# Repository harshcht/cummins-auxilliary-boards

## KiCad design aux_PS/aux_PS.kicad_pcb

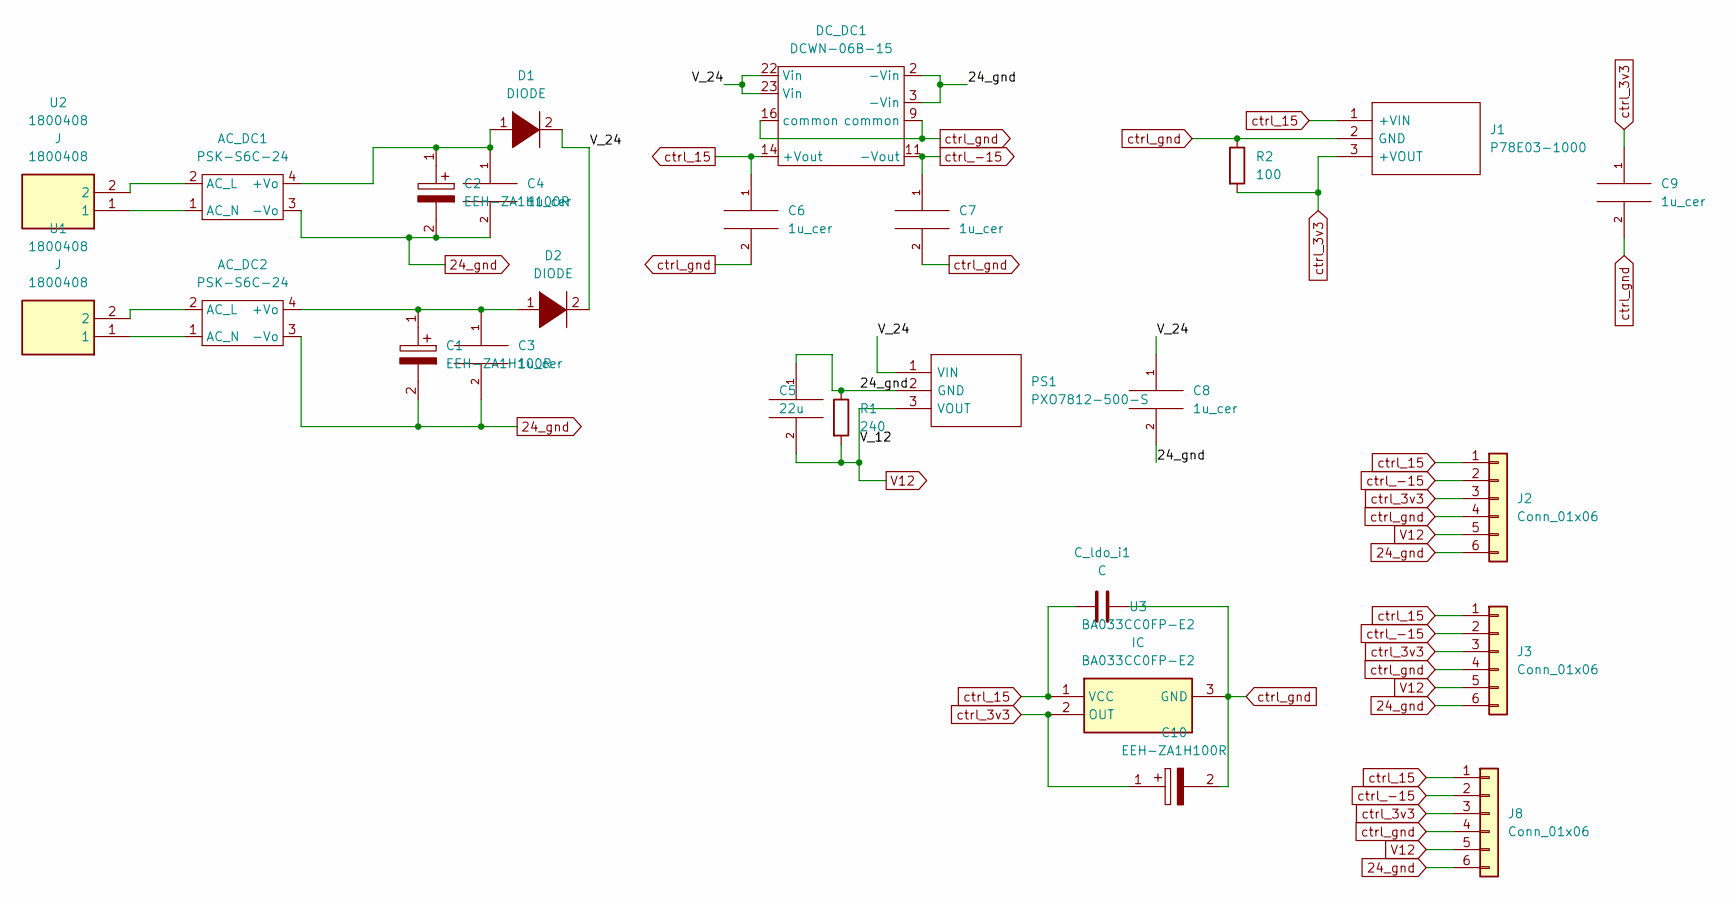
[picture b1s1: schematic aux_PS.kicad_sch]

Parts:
AC_DC1, AC_DC2: PSK-S6C-24; PSKS6C24
C1, C2, C10: EEH-ZA1H100R; EEHZA1H100R; Mouser Part Number 667-EEH-ZA1H100R
C3, C4, C6, C7, C8, C9: 1u_cer; C_1206_3216Metric_Pad1.33x1.80mm_HandSolder
C5: 22u; R_1206_3216Metric_Pad1.30x1.75mm_HandSolder
C_ldo_i1: C; C_1206_3216Metric_Pad1.33x1.80mm_HandSolder
D1, D2: DIODE; D_1206_3216Metric_Pad1.42x1.75mm_HandSolder
DC_DC1: DCWN-06B-15; DCWN06B15
J1: P78E03-1000; P78E031000; Mouser Part Number 490-P78E03-1000
J2, J3, J8: Conn_01x06; PinSocket_1x06_P2.54mm_Vertical
PS1: PXO7812-500-S; PXO7812500S; Mouser Part Number 490-PXO7812-500-S
R1: 240; R_1206_3216Metric_Pad1.30x1.75mm_HandSolder
R2: 100; R_1206_3216Metric_Pad1.30x1.75mm_HandSolder
U1, U2: 1800408; Mouser Part Number 651-1800408
U3: BA033CC0FP-E2; ROHM_TO-252-3; Mouser Part Number 755-BA033CC0FP-E2

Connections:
24_gnd: AC_DC1.3 (-Vo), AC_DC2.3 (-Vo), C1.2, C2.2, C3.2, C4.2, C5.1, C8.2, DC_DC1.2 (-Vin), DC_DC1.3 (-Vin), J2.6, J3.6, J8.6, PS1.2 (GND), R1.1
/V_24: C8.1, D1.2 (A), D2.2 (A), DC_DC1.22 (Vin), DC_DC1.23 (Vin), PS1.1 (VIN)
unnamed: AC_DC1.1 (AC_N), U2.1
unnamed: AC_DC1.2 (AC_L), U2.2
unnamed: AC_DC1.4 (+Vo), C2.1, C4.1, D1.1 (K)
unnamed: AC_DC2.1 (AC_N), U1.1
unnamed: AC_DC2.2 (AC_L), U1.2
unnamed: AC_DC2.4 (+Vo), C1.1, C3.1, D2.1 (K)
V12: C5.2, J2.5, J3.5, J8.5, PS1.3 (VOUT), R1.2
ctrl_3v3: C9.1, C10.1, J1.3 (+VOUT), J2.3, J3.3, J8.3, R2.2, U3.2 (OUT)
ctrl_15: C6.1, C_ldo_i1.2, DC_DC1.14 (+Vout), J1.1 (+VIN), J2.1, J3.1, J8.1, U3.1 (VCC)
ctrl_-15: C7.1, DC_DC1.11 (-Vout), J2.2, J3.2, J8.2
ctrl_gnd: C6.2, C7.2, C9.2, C10.2, C_ldo_i1.1, DC_DC1.9 (common), DC_DC1.16 (common), J1.2 (GND), J2.4, J3.4, J8.4, R2.1, U3.3 (GND)

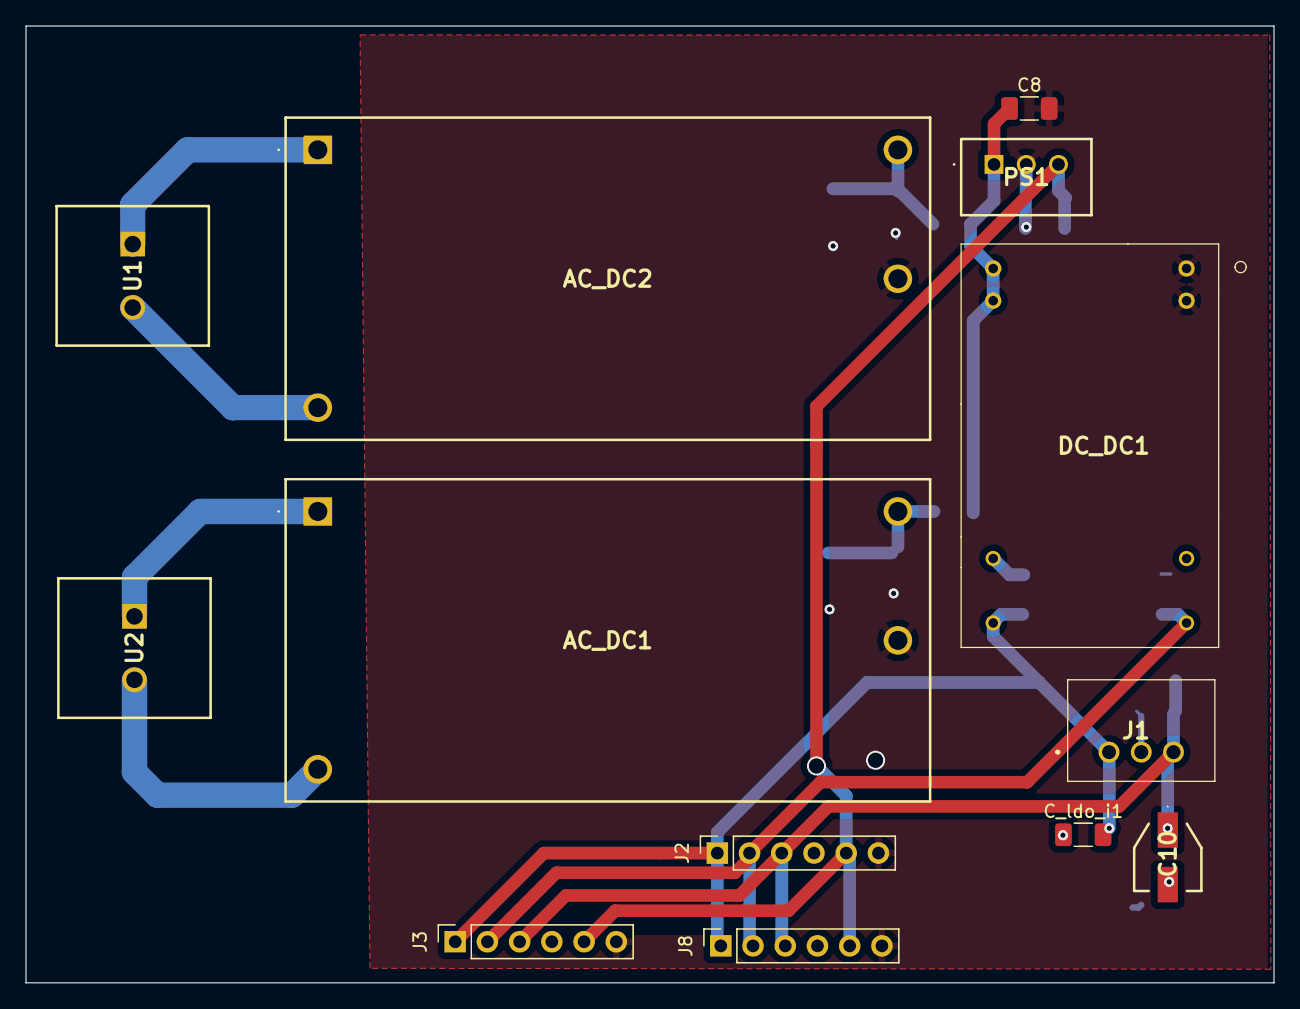
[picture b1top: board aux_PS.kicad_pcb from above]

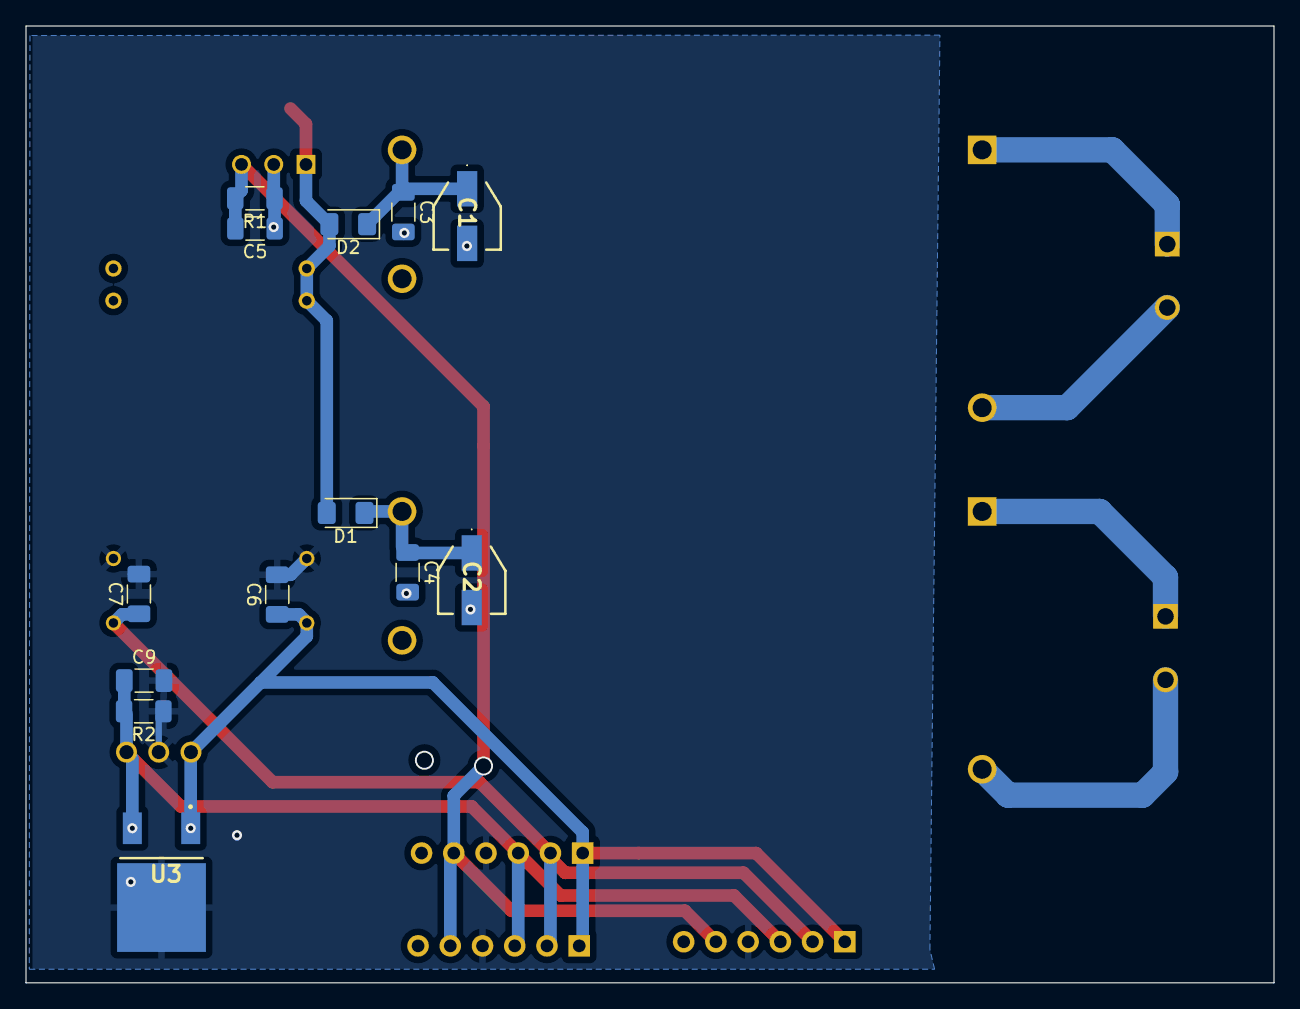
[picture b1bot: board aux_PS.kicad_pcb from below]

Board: 2 copper layers, 98.4 x 75.4 mm, 26 parts (13 on the bottom side), 13 nets.

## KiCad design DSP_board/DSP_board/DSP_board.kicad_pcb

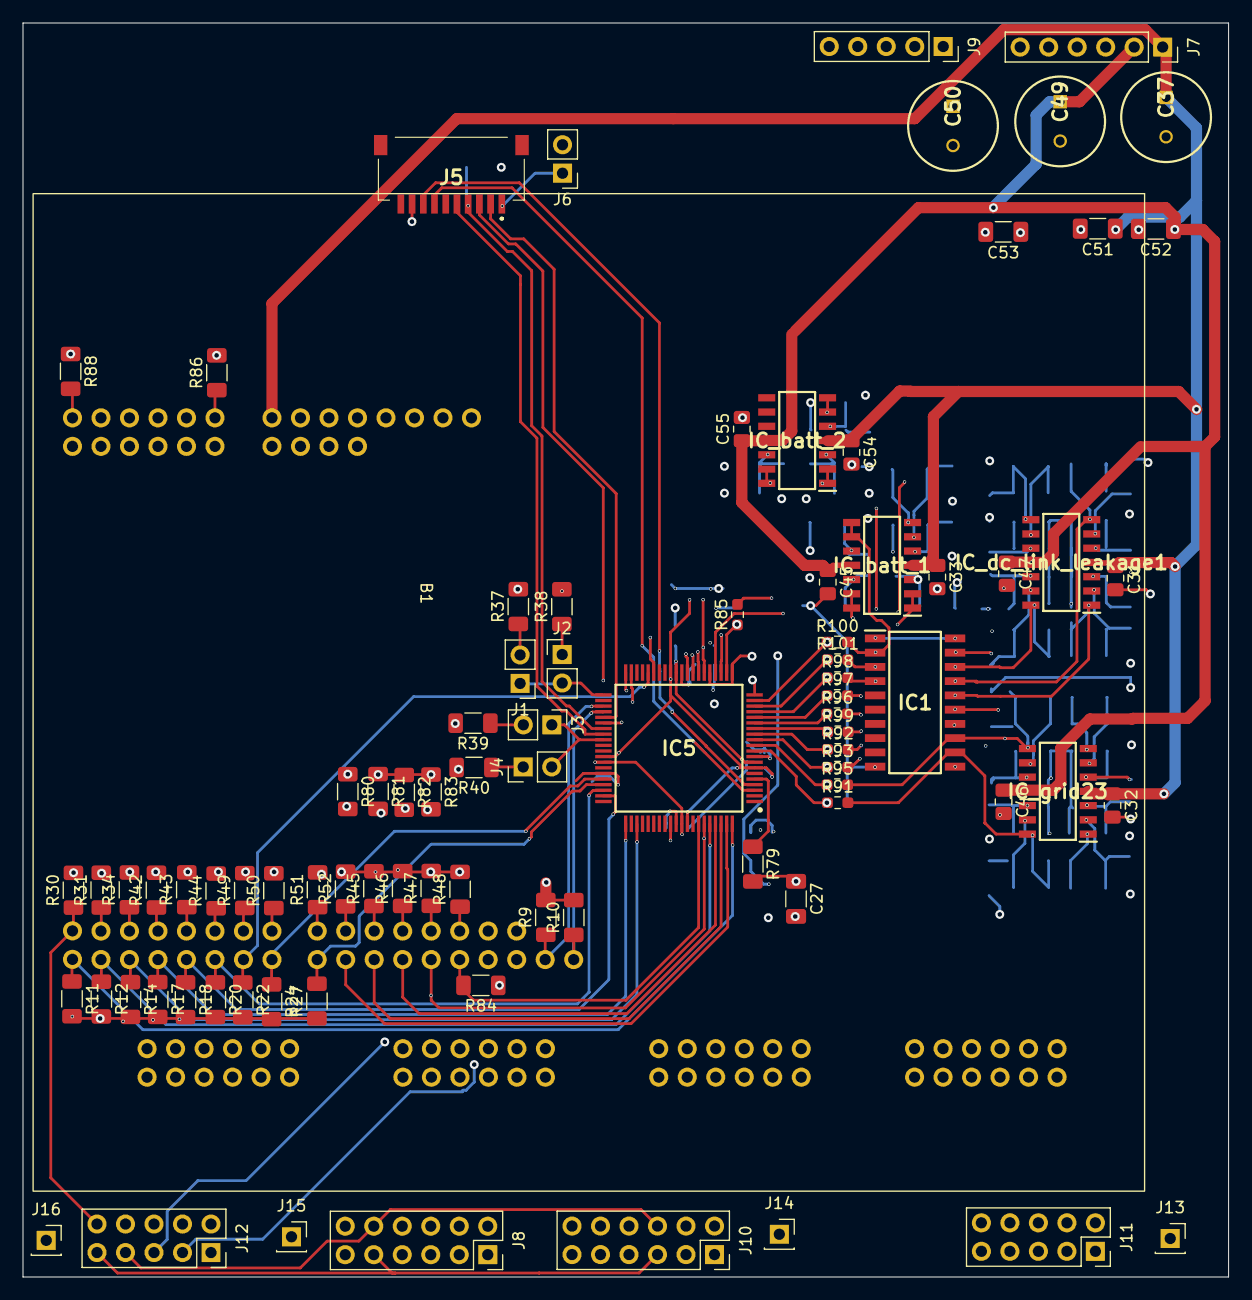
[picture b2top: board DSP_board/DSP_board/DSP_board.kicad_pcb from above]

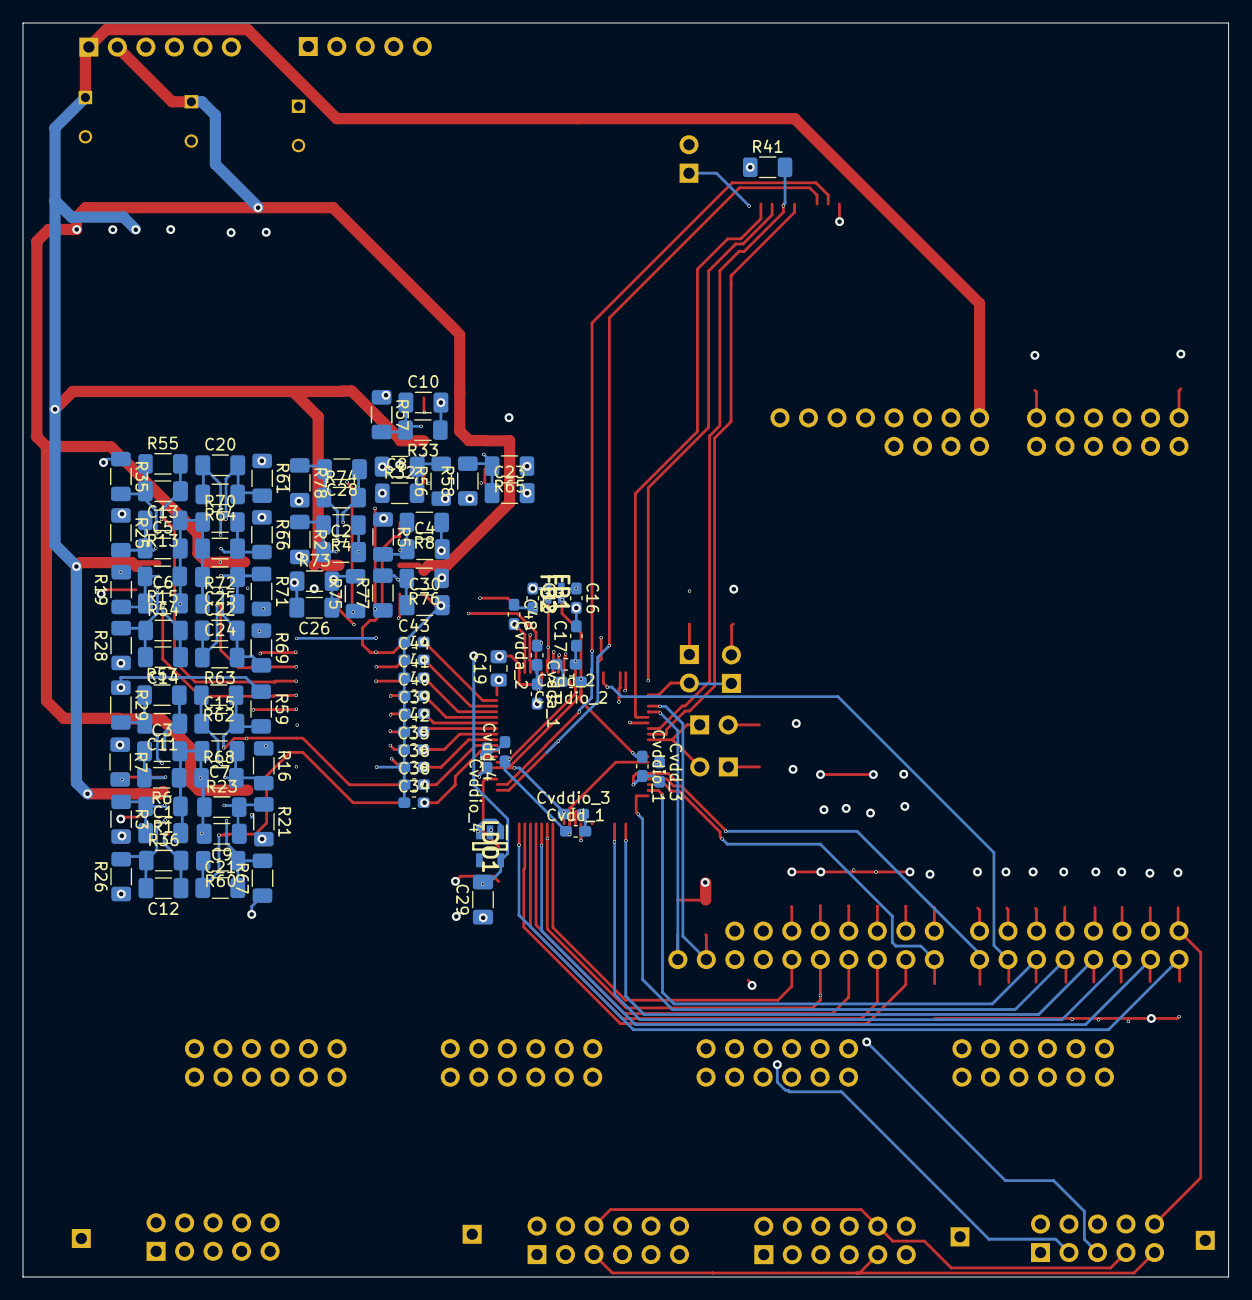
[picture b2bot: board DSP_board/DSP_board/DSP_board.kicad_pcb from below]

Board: 4 copper layers, 107.4 x 111.8 mm, 188 parts (102 on the bottom side), 122 nets.

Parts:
B1: Arty-S7
C1, C2, C3, C4, C5, C6, C7, C8, C9, C10, C11, C12, C13, C14, C15, C20, C21, C22, C23, C24, C25, C26, C27, C28, C29, C30, C51, C52, C53: CAP; C_1206_3216Metric_Pad1.33x1.80mm_HandSolder
C16, C17: 10u; C_0603_1608Metric_Pad1.08x0.95mm_HandSolder
C18: 2.2u; C_0603_1608Metric_Pad1.08x0.95mm_HandSolder
C19: C; C_0805_2012Metric_Pad1.18x1.45mm_HandSolder
C31, C32, C33, C45, C46, C47, C54, C55: CAP; C_0805_2012Metric_Pad1.18x1.45mm_HandSolder
C34, C35, C36, C38, C39, C40, C41, C42, C43, C44, C48: CAP; C_0603_1608Metric_Pad1.08x0.95mm_HandSolder
C37, C49, C50: ESK107M050AG3EA; CAPPRD350W60D800H1250
Cvdd_1, Cvdd_2, Cvdd_3, Cvdd_4: 0.1u; C_0603_1608Metric_Pad1.08x0.95mm_HandSolder
Cvdda_1, Cvdda_2: 0.1u; C_0603_1608Metric_Pad1.08x0.95mm_HandSolder
Cvddio_1, Cvddio_2, Cvddio_3, Cvddio_4: 0.1u; C_0603_1608Metric_Pad1.08x0.95mm_HandSolder
FB1: BKP1005HS221-T; BEADC1005X55N
FB2: MPZ1005S600CT000; BEADC1005X55N
IC1: SN74S1053NSR; sn74
IC5: F280025CPNQR; f280025c
IC_batt_1, IC_batt_2: LM324DR; SOIC127P600X175-14N
IC_dc_link_leakage1: LM324DR; SOIC127P600X175-14N
IC_grid23: LM324DR; SOIC127P600X175-14N
J1, J2, J3, J4, J6: Conn_01x02; PinHeader_1x02_P2.54mm_Vertical
J5: 1-84981-0; 1849810
J7: Conn_01x06; PinSocket_1x06_P2.54mm_Vertical
J8, J10: Conn_02x06_Odd_Even; PinSocket_2x06_P2.54mm_Vertical
J9: Conn_01x05; PinSocket_1x05_P2.54mm_Vertical
J11, J12: Conn_02x05_Odd_Even; PinSocket_2x05_P2.54mm_Vertical
J13, J14, J15, J16: Conn_01x01_Female; PinSocket_1x01_P2.54mm_Vertical
LDO1: NCV8114ASN165T1G; SOT95P275X110-5N
R1, R2, R3, R4, R5, R6, R7, R8, R9, R10, R11, R12, R13, R14, R15, R16, R17, R18, R19, R20, R21, R22, R23, R24, R25, R26, R27, R28, R29, R30, R31, R32, R33, R34, R35, R36, R37, R38, R39, R40, R41, R42, R43, R44, R45, R46, R47, R48, R49, R50, R51, R52, R53, R54, R55, R56, R57, R58, R59, R60, R61, R62, R63, R64, R65, R66, R67, R68, R69, R70, R71, R72, R73, R74, R75, R76, R77, R78, R79, R80, R81, R82, R83, R84, R86, R88: R; R_1206_3216Metric_Pad1.30x1.75mm_HandSolder
R85, R91, R92, R93, R95, R96, R97, R98, R99, R100, R101: R; R_0603_1608Metric_Pad0.98x0.95mm_HandSolder

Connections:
/controller_sheet/en_dab: B1.51 (IO8), IC5.57 (GPIO42), R27.2
/controller_sheet/en_vsi: B1.52 (IO7), IC5.56 (GPIO39), R24.1
/controller_sheet/pwmVSI1: B1.57 (IO2), IC5.63 (GPIO0), R14.1
/controller_sheet/pwmVSI2: B1.56 (IO3), IC5.61 (GPIO2), R17.1
/controller_sheet/pwmVSI3: B1.55 (IO4), IC5.59 (GPIO4), R18.1
/controller_sheet/pwm_daba1: B1.59 (IO0), IC5.80 (GPIO6), R11.1
/controller_sheet/pwm_daba2: B1.54 (IO5), IC5.58 (GPIO8), R20.1
/controller_sheet/pwm_dabb1: B1.58 (IO1), IC5.76 (GPIO10), R12.1
/controller_sheet/pwm_dabb2: B1.53 (IO6), IC5.36 (GPIO12), R22.1
ADC1: IC5.23 (A7C3), IC_batt_1.1 (1OUT), IC_batt_1.2 (1IN-)
ADC2: IC5.24 (A8C11), IC_batt_1.13 (4IN-), IC_batt_1.14 (4OUT)
ADC3: IC5.27 (A4C14), IC_batt_2.1 (1OUT), IC_batt_2.2 (1IN-)
ADC4: IC5.28 (A9C8), IC_batt_2.6 (2IN-), IC_batt_2.7 (2OUT)
ADC5: IC5.29 (A10C10), IC_batt_2.13 (4IN-), IC_batt_2.14 (4OUT)
Analog_in1: J9.1, R75.1
Analog_in2: J9.2, R77.1
Analog_in3: J9.3, R56.1
Analog_in4: J9.4, R57.1
Analog_in5: J9.5, R58.1
DAB1PWM11: B1.35 (IO32), J8.6, R49.1
DAB1PWM12: B1.34 (IO33), J8.5, R50.1
DAB1PWM21: B1.33 (IO34), J8.4, R51.1
DAB1PWM22: B1.32 (IO35), J8.3, R52.1
DAB2_PWM11: B1.31 (IO36), J10.12, R45.1
DAB2_PWM12: B1.30 (IO37), J10.11, R46.1
DAB2_PWM21: B1.29 (IO38), J10.10, R47.1
DAB2_PWM22: B1.28 (IO39), J10.9, R48.1
I_leackage: C22.1, IC1.18 (D15), IC_dc_link_leakage1.14 (4OUT), R63.2, R97.2
I_leackage_f: C40.2, IC5.16 (A11C0), R97.1
Igrid1: J11.3, R19.2
Igrid1_sense: C14.1, IC1.16 (D13), IC_dc_link_leakage1.1 (1OUT), R54.2, R99.2
Igrid1_sense_f: C42.2, IC5.14 (A15C7), R99.1
Igrid2: J11.5, R21.2
Igrid2_sense: C21.1, IC1.12 (D09), IC_grid23.14 (4OUT), R60.2, R91.2
Igrid2_sense_f: C34.2, IC5.10 (A6), R91.1
Igrid3: J11.1, R3.2
Igrid3_sense: C12.1, IC1.14 (D11), IC_grid23.1 (1OUT), R36.2, R93.2
Igrid3_sense_f: C36.2, IC5.12 (A3C5), R93.1
unnamed: C1.1, IC_grid23.3 (1IN+), R1.2, R3.1
unnamed: C2.1, IC_batt_1.5 (2IN+), R2.1, R4.2
unnamed: C3.1, IC_grid23.5 (2IN+), R6.2, R7.2
unnamed: C4.1, IC_batt_1.10 (3IN+), R5.2, R8.2
unnamed: C5.1, IC_dc_link_leakage1.5 (2IN+), R13.2, R25.2
unnamed: C6.1, IC_dc_link_leakage1.3 (1IN+), R15.2, R19.1
unnamed: C7.1, IC_grid23.10 (3IN+), R16.2, R68.2
unnamed: C8.1, IC_batt_2.3 (1IN+), R32.2, R56.2
unnamed: C9.1, IC_grid23.12 (4IN+), R21.1, R23.2
unnamed: C10.1, IC_batt_2.5 (2IN+), R33.2, R57.2
unnamed: C11.2, IC_grid23.6 (2IN-), R29.2, R53.1
unnamed: C12.2, IC_grid23.2 (1IN-), R26.2, R36.1
unnamed: C13.2, IC_dc_link_leakage1.6 (2IN-), R35.2, R55.1
unnamed: C14.2, IC_dc_link_leakage1.2 (1IN-), R28.2, R54.1
unnamed: C15.1, IC_grid23.9 (3IN-), R62.2
unnamed: C19.1, IC5.20 (VREFHI)
unnamed: C20.1, IC_dc_link_leakage1.9 (3IN-), R64.2
unnamed: C21.2, IC_grid23.13 (4IN-), R60.1, R67.2
unnamed: C22.2, IC_dc_link_leakage1.13 (4IN-), R63.1, R69.2
unnamed: C23.1, IC_batt_2.12 (4IN+), R58.2, R65.2
unnamed: C24.1, IC_dc_link_leakage1.10 (3IN+), R66.2, R70.2
unnamed: C25.1, IC_dc_link_leakage1.12 (4IN+), R71.1, R72.2
unnamed: C26.1, IC_batt_1.3 (1IN+), R73.2, R75.2
unnamed: C28.2, IC_batt_1.6 (2IN-), R74.1, R78.1
unnamed: C30.1, IC_batt_1.12 (4IN+), R76.2, R77.2
unnamed: IC5.5 (XRSN), R79.1
unnamed: IC5.41 (GPIO24), J1.1, J2.2
unnamed: IC5.49 (GPIO32), J3.1, J4.2
unnamed: J1.2, R37.1
unnamed: J2.1, R38.1
unnamed: J3.2, R39.1
unnamed: J4.1, R40.1
unnamed: J5.1, J6.1
OCD_grid1: B1.14 (A0), IC5.35 (GPIO13), J11.10, R86.1
OCD_leakage: B1.48 (IO11), IC5.77 (GPIO34), J8.11, R82.2
SCITX: IC5.3 (GPIO29), J5.7
SCL: B1.42 (SCL), IC5.44 (GPIO27), J8.9, J10.5, J12.9, R10.1
SCiRX: IC5.4 (GPIO28), J5.8
SDA: B1.43 (SDA), IC5.43 (GPIO26), J8.10, J10.6, J12.7, R9.1
TCK: IC5.45 (TCK), J5.2
TDI: IC5.48 (GPIO35/TDI), J5.5
TDO: IC5.46 (GPIO37/TDO), J5.3
TMS: IC5.47 (TMS), J5.4, R41.2
VDD: C17.1, Cvdd_1.1, Cvdd_2.1, Cvdd_3.1, Cvdd_4.1, IC5.8 (VDD_1), IC5.31 (VDD_2), IC5.53 (VDD_3), IC5.71 (VDD_4)
VDDA: Cvdda_1.1, Cvdda_2.1, FB2.1, IC5.26 (VDDA)
VDDIO: Cvddio_1.1, Cvddio_2.1, Cvddio_3.1, Cvddio_4.1, FB1.1, IC5.7 (VDDIO_1), IC5.32 (VDDIO_2), IC5.52 (VDDIO_3), IC5.72 (VDDIO_4)
VSI11: B1.41 (IO28), J12.10, R30.1
VSI12: B1.40 (IO27), J12.8, R31.1
VSI21: B1.39 (IO28), J12.6, R34.1
VSI22: B1.38 (IO29), J12.4, R42.1
VSI31: B1.37 (IO30), J12.2, R43.1
VSI32: B1.36 (IO31), J12.1, R44.1
V_dc_link: J8.2, R66.1
Vdc_link: C20.2, IC1.4 (D03), IC_dc_link_leakage1.8 (3OUT), R61.2, R64.1, R98.2
Vdc_link_f: C41.2, IC5.17 (A5C2), R98.1
Vgrid1: J11.4, R25.1
Vgrid1_sense: C13.1, IC1.17 (D14), IC_dc_link_leakage1.7 (2OUT), R55.2, R96.2
Vgrid1_sense_f: C39.2, IC5.15 (A14C4), R96.1
Vgrid2: J11.6, R16.1
Vgrid2_sense: C15.2, IC1.13 (D10), IC_grid23.8 (3OUT), R59.2, R62.1, R95.2
Vgrid2_sense_f: C38.2, IC5.11 (C6), R95.1
Vgrid3: J11.2, R7.1
Vgrid3_sense: C11.1, IC1.15 (D12), IC_grid23.7 (2OUT), R53.2, R92.2
Vgrid3_sense_f: C35.2, IC5.13 (A2C9), R92.1
batt_V_sense: IC1.2 (D01), IC_batt_1.8 (3OUT), IC_batt_1.9 (3IN-), R100.2
batt_V_sense_f: C43.2, IC5.19 (A0C15), R100.1
batt_curr_0: J10.1, R2.2
batt_curr_sense: C28.1, IC1.3 (D02), IC_batt_1.7 (2OUT), R74.2, R101.2
batt_curr_sense_f: C44.2, IC5.18 (A1), R101.1
batt_fault: B1.27 (IO40), IC5.39 (GPIO16), J10.3
batt_ready: B1.26 (IO41), IC5.40 (GPIO17), J10.4
batt_v: J10.2, R5.1
ctrl_3v3: C16.1, C18.1, C27.1, C50.1, C53.1, FB1.2, FB2.2, IC1.1 (VCC_1), IC1.20 (VCC_2), J6.2, J7.3, LDO1.1 (IN), LDO1.3 (EN), R9.2, R10.2, R37.2, R39.2, R41.1, R79.2
ctrl_15: B1.8 (VIN), C31.1, C32.1, C33.1, C37.1, C51.1, C54.1, IC_batt_1.4 (VCC), IC_batt_2.4 (VCC), IC_dc_link_leakage1.4 (VCC), IC_grid23.4 (VCC), J7.1
ctrl_-15: C45.1, C46.1, C47.1, C49.1, C52.1, C55.1, IC_batt_1.11 (GND), IC_batt_2.11 (GND), IC_dc_link_leakage1.11 (GND), IC_grid23.11 (GND), J7.2
ctrl_gnd: B1.6 (GND), B1.7 (GND), C4.2, C8.2, C10.2, C16.2, C17.2, C18.2, C19.2, C23.2, C26.2, C27.2, C29.1, C30.2, C31.2, C32.2, C33.2, C34.1, C35.1, C36.1, C37.2, C38.1, C39.1, C40.1, C41.1, C42.1, C43.1, C44.1, C45.2, C46.2, C47.2, C48.1, C49.2, C50.2, C51.2, C52.2, C53.2, C54.2, C55.2, Cvdd_1.2, Cvdd_2.2, Cvdd_3.2, Cvdd_4.2, Cvdda_1.2, Cvdda_2.2, Cvddio_1.2, Cvddio_2.2, Cvddio_3.2, Cvddio_4.2, IC1.10 (GND_1), IC1.11 (GND_2), IC5.9 (VSS_1), IC5.21 (VREFLO), IC5.25 (VSSA), IC5.30 (VSS_2), IC5.55 (VSS_3), IC5.70 (VSS_4), J5.9, J7.4, J8.12, J10.8, J11.7, J13.1, J14.1, J15.1, J16.1, LDO1.2 (GND), R8.1, R11.2, R12.2, R14.2, R17.2, R18.2, R20.2, R22.2, R24.2, R26.1, R27.1, R28.1, R29.1, R30.2, R31.2, R32.1, R33.1, R34.2, R35.1, R38.2, R40.2, R42.2, R43.2, R44.2, R45.2, R46.2, R47.2, R48.2, R49.2, R50.2, R51.2, R52.2, R59.1, R61.1, R65.1, R67.1, R69.1, R73.1, R76.1, R78.2, R80.1, R81.1, R82.1, R83.1, R84.1, R86.2, R88.1
curr_leakeage_i: J8.1, R71.2
dc_fault: B1.49 (IO10), IC5.78 (GPIO15), J8.7, R81.2
dc_ready: B1.50 (IO9), IC5.79 (GPIO14), J8.8, R80.2
offset_f: C48.2, IC5.22 (A12C1), R85.1
offset_v: C1.2, C2.2, C3.2, C5.2, C6.2, C7.2, C9.2, C24.2, C25.2, C29.2, IC1.19 (D16), LDO1.5 (OUT), R1.1, R4.1, R6.1, R13.1, R15.1, R23.1, R68.1, R70.1, R72.1, R85.2
relay_1: B1.19 (A5), IC5.69 (GPIO44), J11.8, R88.2
vsi_fault: B1.47 (IO12), IC5.75 (GPIO9), J12.5, R83.2
vsi_ready: B1.46 (IO13), IC5.74 (GPIO5), J12.3, R84.2

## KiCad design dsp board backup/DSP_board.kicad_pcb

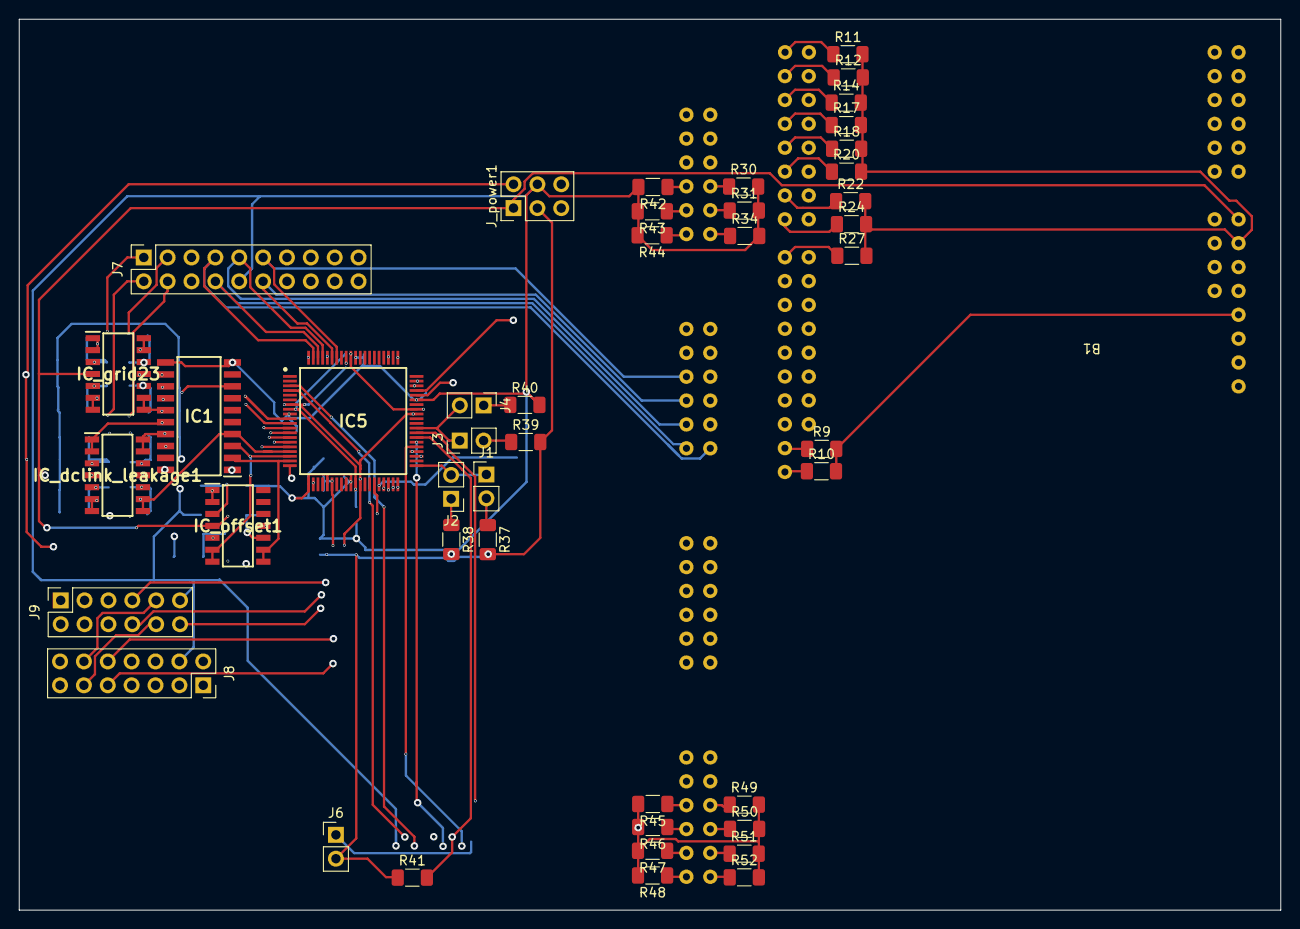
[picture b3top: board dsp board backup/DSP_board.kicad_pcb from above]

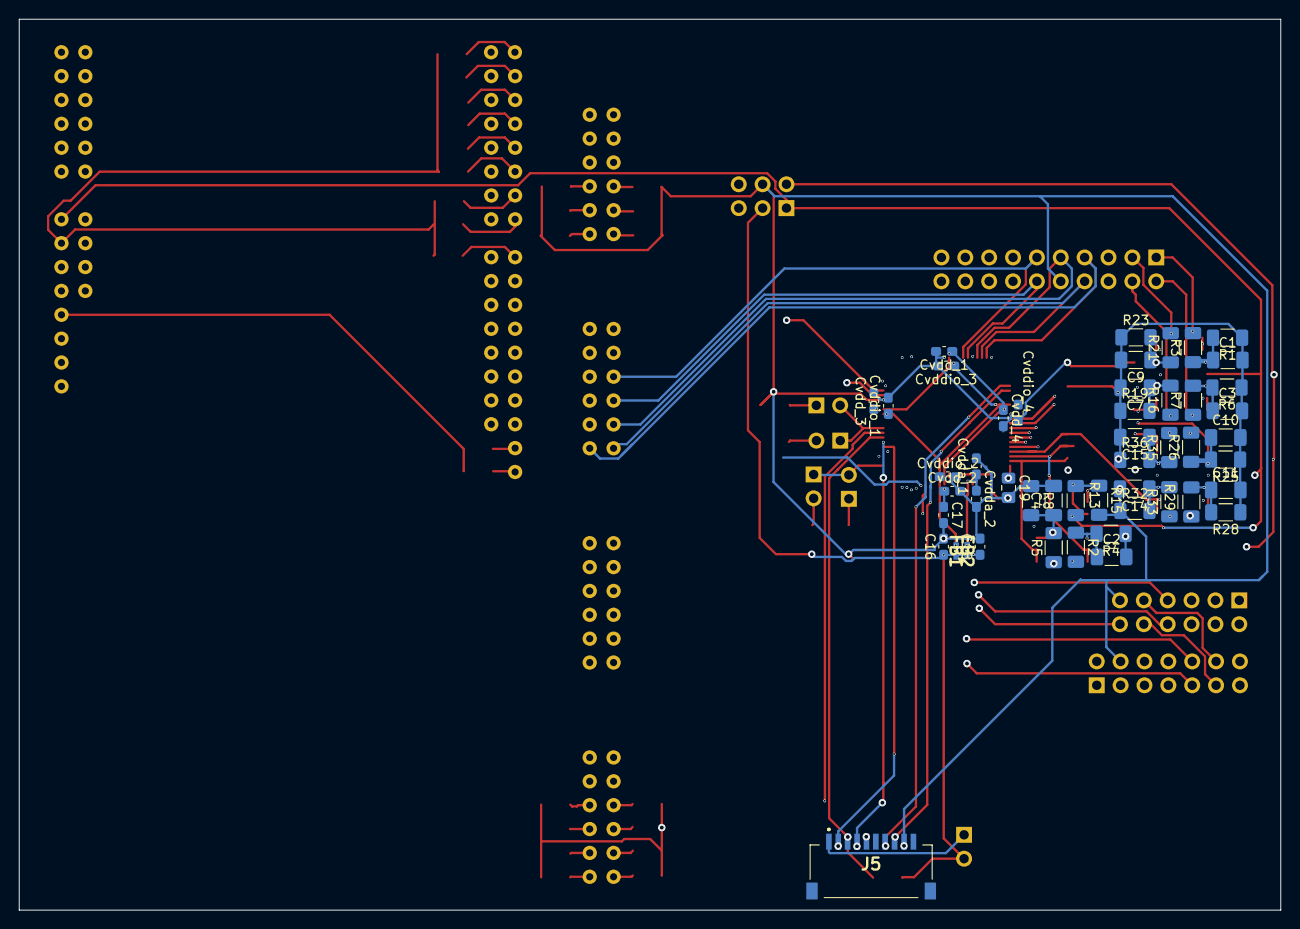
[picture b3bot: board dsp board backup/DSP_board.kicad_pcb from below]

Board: 4 copper layers, 134.2 x 94.8 mm, 94 parts (49 on the bottom side), 89 nets.

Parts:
B1: Arty-S7
C1, C2, C3, C4, C7, C9, C10, C11, C14, C15: CAP; C_1206_3216Metric_Pad1.33x1.80mm_HandSolder
C16, C17: 10u; C_0603_1608Metric_Pad1.08x0.95mm_HandSolder
C18: 2.2u; C_0603_1608Metric_Pad1.08x0.95mm_HandSolder
C19: C; C_0805_2012Metric_Pad1.18x1.45mm_HandSolder
Cvdd_1, Cvdd_2, Cvdd_3, Cvdd_4: 0.1u; C_0603_1608Metric_Pad1.08x0.95mm_HandSolder
Cvdda_1, Cvdda_2: 0.1u; C_0603_1608Metric_Pad1.08x0.95mm_HandSolder
Cvddio_1, Cvddio_2, Cvddio_3, Cvddio_4: 0.1u; C_0603_1608Metric_Pad1.08x0.95mm_HandSolder
FB1: BKP1005HS221-T; BEADC1005X55N
FB2: MPZ1005S600CT000; BEADC1005X55N
IC1: SN74S1053NSR; sn74
IC5: F280025CPNQR; f280025c
IC_dclink_leakage1: LM324DR; SOIC127P600X175-14N
IC_grid23: LM324DR; SOIC127P600X175-14N
IC_offset1: LM324DR; SOIC127P600X175-14N
J1, J2, J3, J4, J6: Conn_01x02; PinHeader_1x02_P2.54mm_Vertical
J5: 1-84981-0; 1849810
J7: Conn_02x10_Odd_Even; PinSocket_2x10_P2.54mm_Vertical
J8: Conn_02x06_Odd_Even; PinSocket_2x07_P2.54mm_Vertical
J9: Conn_02x06_Odd_Even; PinSocket_2x06_P2.54mm_Vertical
J_power1: Conn_02x03_Counter_Clockwise; PinHeader_2x03_P2.54mm_Vertical
R1, R2, R3, R4, R5, R6, R7, R8, R9, R10, R11, R12, R13, R14, R15, R16, R17, R18, R19, R20, R21, R22, R23, R24, R25, R26, R27, R28, R29, R30, R31, R32, R33, R34, R35, R36, R37, R38, R39, R40, R41, R42, R43, R44, R45, R46, R47, R48, R49, R50, R51, R52: R; R_1206_3216Metric_Pad1.30x1.75mm_HandSolder

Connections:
/controller_sheet/en_dab: B1.51 (IO8), IC5.56 (GPIO39), R27.1
/controller_sheet/en_vsi: B1.52 (IO7), IC5.57 (GPIO42), R24.1
/controller_sheet/pwmVSI1: B1.57 (IO2), IC5.63 (GPIO0), R14.1
/controller_sheet/pwmVSI2: B1.56 (IO3), IC5.61 (GPIO2), R17.1
/controller_sheet/pwmVSI3: B1.55 (IO4), IC5.59 (GPIO4), R18.1
/controller_sheet/pwm_daba1: B1.59 (IO0), IC5.80 (GPIO6), R11.1
/controller_sheet/pwm_daba2: B1.54 (IO5), IC5.58 (GPIO8), R20.1
/controller_sheet/pwm_dabb1: B1.58 (IO1), IC5.76 (GPIO10), R12.1
/controller_sheet/pwm_dabb2: B1.53 (IO6), IC5.36 (GPIO12), R22.1
DAB1PWM11: B1.63 (JA4), J9.5, R49.1
DAB1PWM12: B1.62 (JA3), J9.6, R50.1
DAB1PWM21: B1.61 (JA2), J9.3, R51.1
DAB1PWM22: B1.60 (JA1), J9.4, R52.1
DAB2_PWM11: B1.69 (JA10), J8.8, R45.1
DAB2_PWM12: B1.68 (JA9), J8.6, R46.1
DAB2_PWM21: B1.67 (JA8), J8.7, R47.1
DAB2_PWM22: B1.66 (JA7), J8.5, R48.1
FPGA_3v3: B1.4 (3V3), R9.2, R10.2
I_leackage: IC1.17 (D14), IC5.15 (A14C4), IC_dclink_leakage1.13 (4IN-), IC_dclink_leakage1.14 (4OUT)
Igrid1: J7.5, R26.2
Igrid1_sense: IC1.16 (D13), IC5.14 (A15C7), IC_dclink_leakage1.1 (1OUT), IC_dclink_leakage1.2 (1IN-)
Igrid2: J7.3, R21.2
Igrid2_sense: IC1.12 (D09), IC5.10 (A6), IC_grid23.13 (4IN-), IC_grid23.14 (4OUT)
Igrid3: J7.1, R3.2
Igrid3_sense: IC1.13 (D10), IC5.11 (C6), IC_grid23.1 (1OUT), IC_grid23.2 (1IN-)
unnamed: C1.1, IC_grid23.3 (1IN+), R1.2, R3.1
unnamed: C2.1, IC_offset1.5 (2IN+), R2.1, R4.2
unnamed: C3.1, IC_grid23.5 (2IN+), R6.2, R7.2
unnamed: C4.1, IC_offset1.10 (3IN+), R5.2, R8.2
unnamed: C7.1, IC_grid23.10 (3IN+), R16.2, R19.2
unnamed: C9.1, IC_grid23.12 (4IN+), R21.1, R23.2
unnamed: C10.1, IC_dclink_leakage1.3 (1IN+), R25.2, R26.1
unnamed: C11.1, IC_dclink_leakage1.5 (2IN+), R28.2, R29.2
unnamed: C14.1, IC_dclink_leakage1.10 (3IN+), R32.2, R33.2
unnamed: C15.1, IC_dclink_leakage1.12 (4IN+), R35.1, R36.2
unnamed: C19.1, IC5.20 (VREFHI)
unnamed: IC5.41 (GPIO24), J1.1, J2.2
unnamed: IC5.49 (GPIO32), J3.1, J4.2
unnamed: IC_offset1.3 (1IN+), R13.1, R15.1
unnamed: J1.2, R37.1
unnamed: J2.1, R38.1
unnamed: J3.2, R39.1
unnamed: J4.1, R40.1
unnamed: J5.1, J6.1
OCD_grd2: B1.90 (JC7), IC5.78 (GPIO15), J7.8
OCD_grid1: B1.84 (JC1), IC5.79 (GPIO14), J7.7
OCD_grid3: B1.91 (JC8), IC5.77 (GPIO34), J7.9
OCD_leakage: IC5.38 (GPIO33), J9.12
SCITX: IC5.3 (GPIO29), J5.7
SCL: B1.42 (SCL), IC5.44 (GPIO27), J7.19, J8.12, J9.9, R10.1
SCiRX: IC5.4 (GPIO28), J5.8
SDA: B1.43 (SDA), IC5.43 (GPIO26), J7.20, J8.11, J9.10, R9.1
TCK: IC5.45 (TCK), J5.2
TDI: IC5.48 (GPIO35/TDI), J5.5
TDO: IC5.46 (GPIO37/TDO), J5.4
TMS: IC5.47 (TMS), J5.3, R41.2
VDD: C17.1, Cvdd_1.1, Cvdd_2.1, Cvdd_3.1, Cvdd_4.1, IC5.8 (VDD_1), IC5.31 (VDD_2), IC5.53 (VDD_3), IC5.71 (VDD_4)
VDDA: Cvdda_1.1, Cvdda_2.1, FB2.1, IC5.26 (VDDA)
VDDIO: Cvddio_1.1, Cvddio_2.1, Cvddio_3.1, Cvddio_4.1, FB1.1, IC5.7 (VDDIO_1), IC5.32 (VDDIO_2), IC5.52 (VDDIO_3), IC5.72 (VDDIO_4)
VSI11: B1.102 (JD7), J7.17, R44.1
VSI12: B1.96 (JD1), J7.18, R34.1
VSI21: B1.103 (JD8), J7.15, R43.1
VSI22: B1.97 (JD2), J7.16, R31.1
VSI31: B1.104 (JD9), J7.13, R42.1
VSI32: B1.98 (JD3), J7.14, R30.1
V_dc_link: J9.2, R33.1
Vdc_link: IC1.4 (D03), IC5.17 (A5C2), IC_dclink_leakage1.8 (3OUT), IC_dclink_leakage1.9 (3IN-)
Vgrid1: J7.6, R29.1
Vgrid1_sense: IC1.18 (D15), IC5.16 (A11C0), IC_dclink_leakage1.6 (2IN-), IC_dclink_leakage1.7 (2OUT)
Vgrid2: J7.4, R16.1
Vgrid2_sense: IC1.15 (D12), IC5.13 (A2C9), IC_grid23.8 (3OUT), IC_grid23.9 (3IN-)
Vgrid3: J7.2, R7.1
Vgrid3_sense: IC1.14 (D11), IC5.12 (A3C5), IC_grid23.6 (2IN-), IC_grid23.7 (2OUT)
batt_V_sense: IC1.2 (D01), IC5.19 (A0C15), IC_offset1.8 (3OUT), IC_offset1.9 (3IN-)
batt_curr_0: J8.1, R2.2
batt_curr_sense: IC1.3 (D02), IC5.18 (A1), IC_offset1.6 (2IN-), IC_offset1.7 (2OUT)
batt_fault: IC5.39 (GPIO16), J8.10
batt_ready: IC5.40 (GPIO17), J8.9
batt_v: J8.2, R5.1
ctrl_3v3: C16.1, C18.1, FB1.2, FB2.2, IC1.1 (VCC_1), IC1.20 (VCC_2), J6.2, J_power1.3, R37.2, R39.2, R41.1
ctrl_15: B1.8 (VIN), IC_dclink_leakage1.4 (VCC), IC_grid23.4 (VCC), IC_offset1.4 (VCC), J_power1.1, R13.2
ctrl_-15: IC_dclink_leakage1.11 (GND), IC_grid23.11 (GND), IC_offset1.11 (GND), J_power1.2
ctrl_gnd: B1.6 (GND), B1.7 (GND), C4.2, C14.2, C16.2, C17.2, C18.2, C19.2, Cvdd_1.2, Cvdd_2.2, Cvdd_3.2, Cvdd_4.2, Cvdda_1.2, Cvdda_2.2, Cvddio_1.2, Cvddio_2.2, Cvddio_3.2, Cvddio_4.2, IC1.10 (GND_1), IC1.11 (GND_2), IC5.9 (VSS_1), IC5.21 (VREFLO), IC5.25 (VSSA), IC5.30 (VSS_2), IC5.55 (VSS_3), IC5.70 (VSS_4), J5.9, J7.10, J8.4, J9.11, J_power1.4, R8.1, R11.2, R12.2, R14.2, R15.2, R17.2, R18.2, R20.2, R22.2, R24.2, R27.2, R30.2, R31.2, R32.1, R34.2, R38.2, R40.2, R42.2, R43.2, R44.2, R45.2, R46.2, R47.2, R48.2, R49.2, R50.2, R51.2, R52.2
curr_leakeage_i: J9.1, R35.2
dc_fault: IC5.37 (GPIO11), J9.8
dc_ready: IC5.35 (GPIO13), J9.7
offset_v: C1.2, C2.2, C3.2, C7.2, C9.2, C10.2, C11.2, C15.2, IC1.8 (D07), IC5.22 (A12C1), IC_offset1.1 (1OUT), IC_offset1.2 (1IN-), R1.1, R4.1, R6.1, R19.1, R23.1, R25.1, R28.1, R36.1
vsi_fault: B1.92 (JC10), IC5.75 (GPIO9), J7.12
vsi_ready: B1.93 (JC10), IC5.74 (GPIO5), J7.11

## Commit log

2023-03-25 including FPGA
2023-04-08 Connecting FPGA ADC pins
2023-04-08 backup
2023-04-10 quad_opamp_placement
2023-04-10 autosaved
2023-04-17 adding diodes
2023-04-17 save
2023-04-17 introduce diode
2023-04-17 adding diode footprint
2023-04-17 adding offset measurements
2023-04-18 connected ADC's
2023-04-24 controller_final
2023-06-02 header design
2023-06-08 review changes
2023-06-09 revie of power board
